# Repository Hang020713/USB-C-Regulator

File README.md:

# About This Project

A compact USB‑C powered boost regulator board based on the MT3608 DC‑DC step‑up converter.

This board is designed for small embedded systems, robotics projects, and portable power applications requiring adjustable output voltage from a USB‑C input source.

---

# 📟 Board Preview

![[pcb]](/images/pcb.png)

---

# 📁 File Structure

<!-- TREEVIEW START -->
```bash
├── USB-C-Regulator.kicad_pcb   # PCB Layout
├── USB-C-Regulator.kicad_pro   # KiCad Project File
├── USB-C-Regulator.kicad_sch   # Schematic
└── README.md
```

## File Descriptions
* `kicad_pcb` - PCB Layout
* `kicad_sch` - Schematic
* `kicad_pro` - KiCad Project Configuration File
<!-- TREEVIEW END -->

---

# 🚀 Getting Started

Requirements
* KiCad 8 (recommended)

Open the `.kicad_pro` file using KiCad 8 to access the full project including schematic and PCB layout.

---

# 🔧 Board Feature

STM32 Board have below features
- [x] Hand-solder friendly footprint design
- [x] MT3608
- [x] USB-C Power Connector
- [x] Adjustable Output Voltage
- [x] Compact PCB Deisgn

---

# ⚙️ Technical Overview

* Input: 5V from USB‑C
* Converter IC: MT3608
* Topology: Boost (Step‑Up) DC‑DC
* Application: Portable power systems, embedded projects, battery-powered devices

# 🧠 Usage

* Step up 5V USB input to higher voltages (e.g., 9V / 12V)
* Power sensors, microcontrollers, or motor drivers
* Serve as a regulated power module in robotics projects
* Integrate into custom embedded designs

## Typical Workflow
1. Manufacture PCB
2. Solder components
3. Adjust output voltage via feedback resistors
4. Verify output with a multimeter before connecting load

⚠️ Always verify output voltage before powering 
sensitive electronics.

---

# 📦 Bill of Materials (BOM)

| Reference | Value | Package / Footprint | Qty |
|-----------|-------|--------------------|-----|
| C1, C3 | 22 µF Capacitor | 1206 SMD | 2 |
| L1 | 22 µH Inductor | 7.3×7.3 mm SMD | 1 |
| D1 | SS34 Schottky Diode | SMA (SMD) | 1 |
| J2 | 2‑Pin Output Header (2.54 mm) | Through‑hole | 1 |
| J3 | USB‑C Receptacle (Power Only, 6‑Pin) | SMD Type‑C | 1 |
| R2 | 2.2 kΩ Resistor | 1206 SMD | 1 |
| R3, R4 | 5.1 kΩ Resistor | 1206 SMD | 2 |
| RV1 | 100 kΩ Trimmer Potentiometer | Bourns 3296W (THT) | 1 |
| U1 | MT3608 Boost Converter IC | SOT‑23‑6 | 1 |

---

# License

MIT License

Feel free to use, modify, and distribute.

---

## 📫 Let's Connect

I'm always interested in collaborating on embedded systems projects, robotics competitions, or autonomous vehicle development!

---

<p align="right">(<a href="#readme-top">Back to Top</a>)</p>

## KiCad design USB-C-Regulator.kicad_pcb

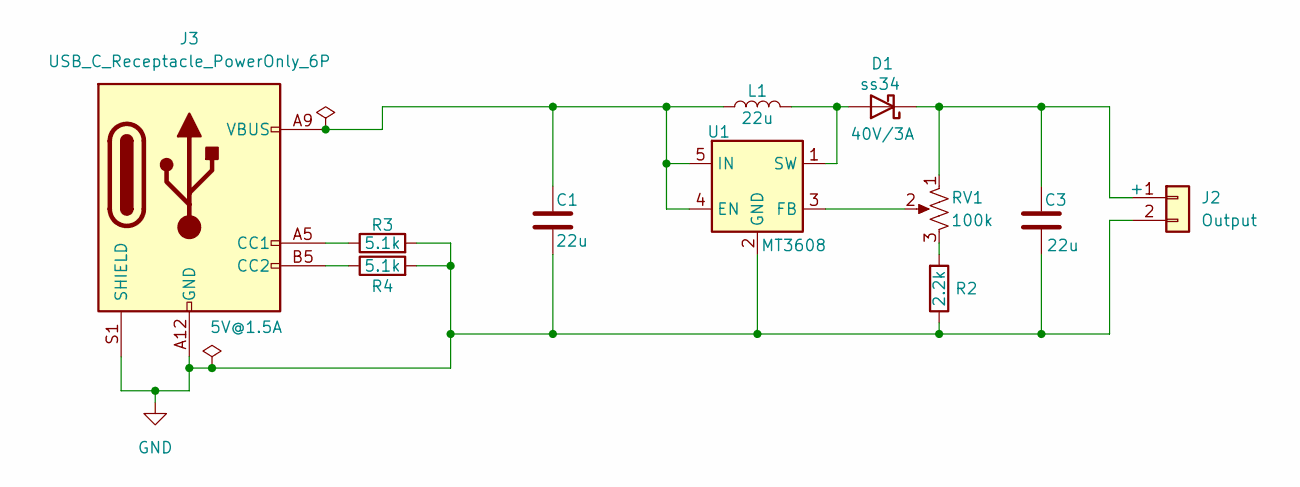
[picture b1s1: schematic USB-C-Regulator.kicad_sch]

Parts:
C1, C3: 22u; C_1206_3216Metric_Pad1.33x1.80mm_HandSolder
D1: ss34; D_SMA_Handsoldering
J2: Output; PinHeader_1x02_P2.54mm_Vertical
J3: USB_C_Receptacle_PowerOnly_6P; USB_C_Receptacle_HRO_TYPE-C-31-M-17
L1: 22u; L_7.3x7.3_H3.5
R2: 2.2k; R_1206_3216Metric_Pad1.30x1.75mm_HandSolder
R3, R4: 5.1k; R_1206_3216Metric_Pad1.30x1.75mm_HandSolder
RV1: 100k; Potentiometer_Bourns_3296W_Vertical
U1: MT3608; SOT-23-6_Handsoldering

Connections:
GND: C1.2, C3.2, J2.2, J3.A12 (GND), J3.B12 (GND), J3.S1 (SHIELD), R2.1, R3.2, R4.2, U1.2 (GND)
unnamed: D1.2 (A), L1.2, U1.1 (SW)
unnamed: C3.1, D1.1 (K), J2.1, RV1.1
unnamed: J3.A5 (CC1), R3.1
unnamed: J3.B5 (CC2), R4.1
unnamed: R2.2, RV1.3
unnamed: C1.1, J3.A9 (VBUS), J3.B9 (VBUS), L1.1, U1.4 (EN), U1.5 (IN)
unnamed: RV1.2, U1.3 (FB)

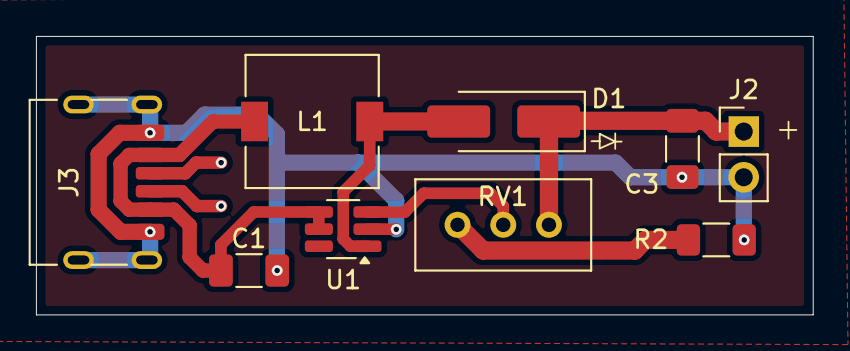
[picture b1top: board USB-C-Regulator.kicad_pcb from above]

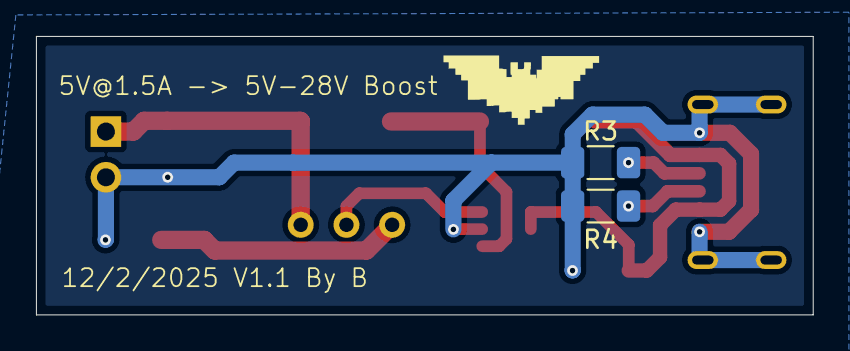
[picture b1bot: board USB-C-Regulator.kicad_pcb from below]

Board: 2 copper layers, 43.2 x 15.5 mm, 11 parts (2 on the bottom side), 8 nets.

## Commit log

2026-04-12 feat: update the files
2026-04-17 chore: update gitignore
2026-04-17 feat: update readme
    Added board preview section
2026-04-17 chore: kicad_pro
